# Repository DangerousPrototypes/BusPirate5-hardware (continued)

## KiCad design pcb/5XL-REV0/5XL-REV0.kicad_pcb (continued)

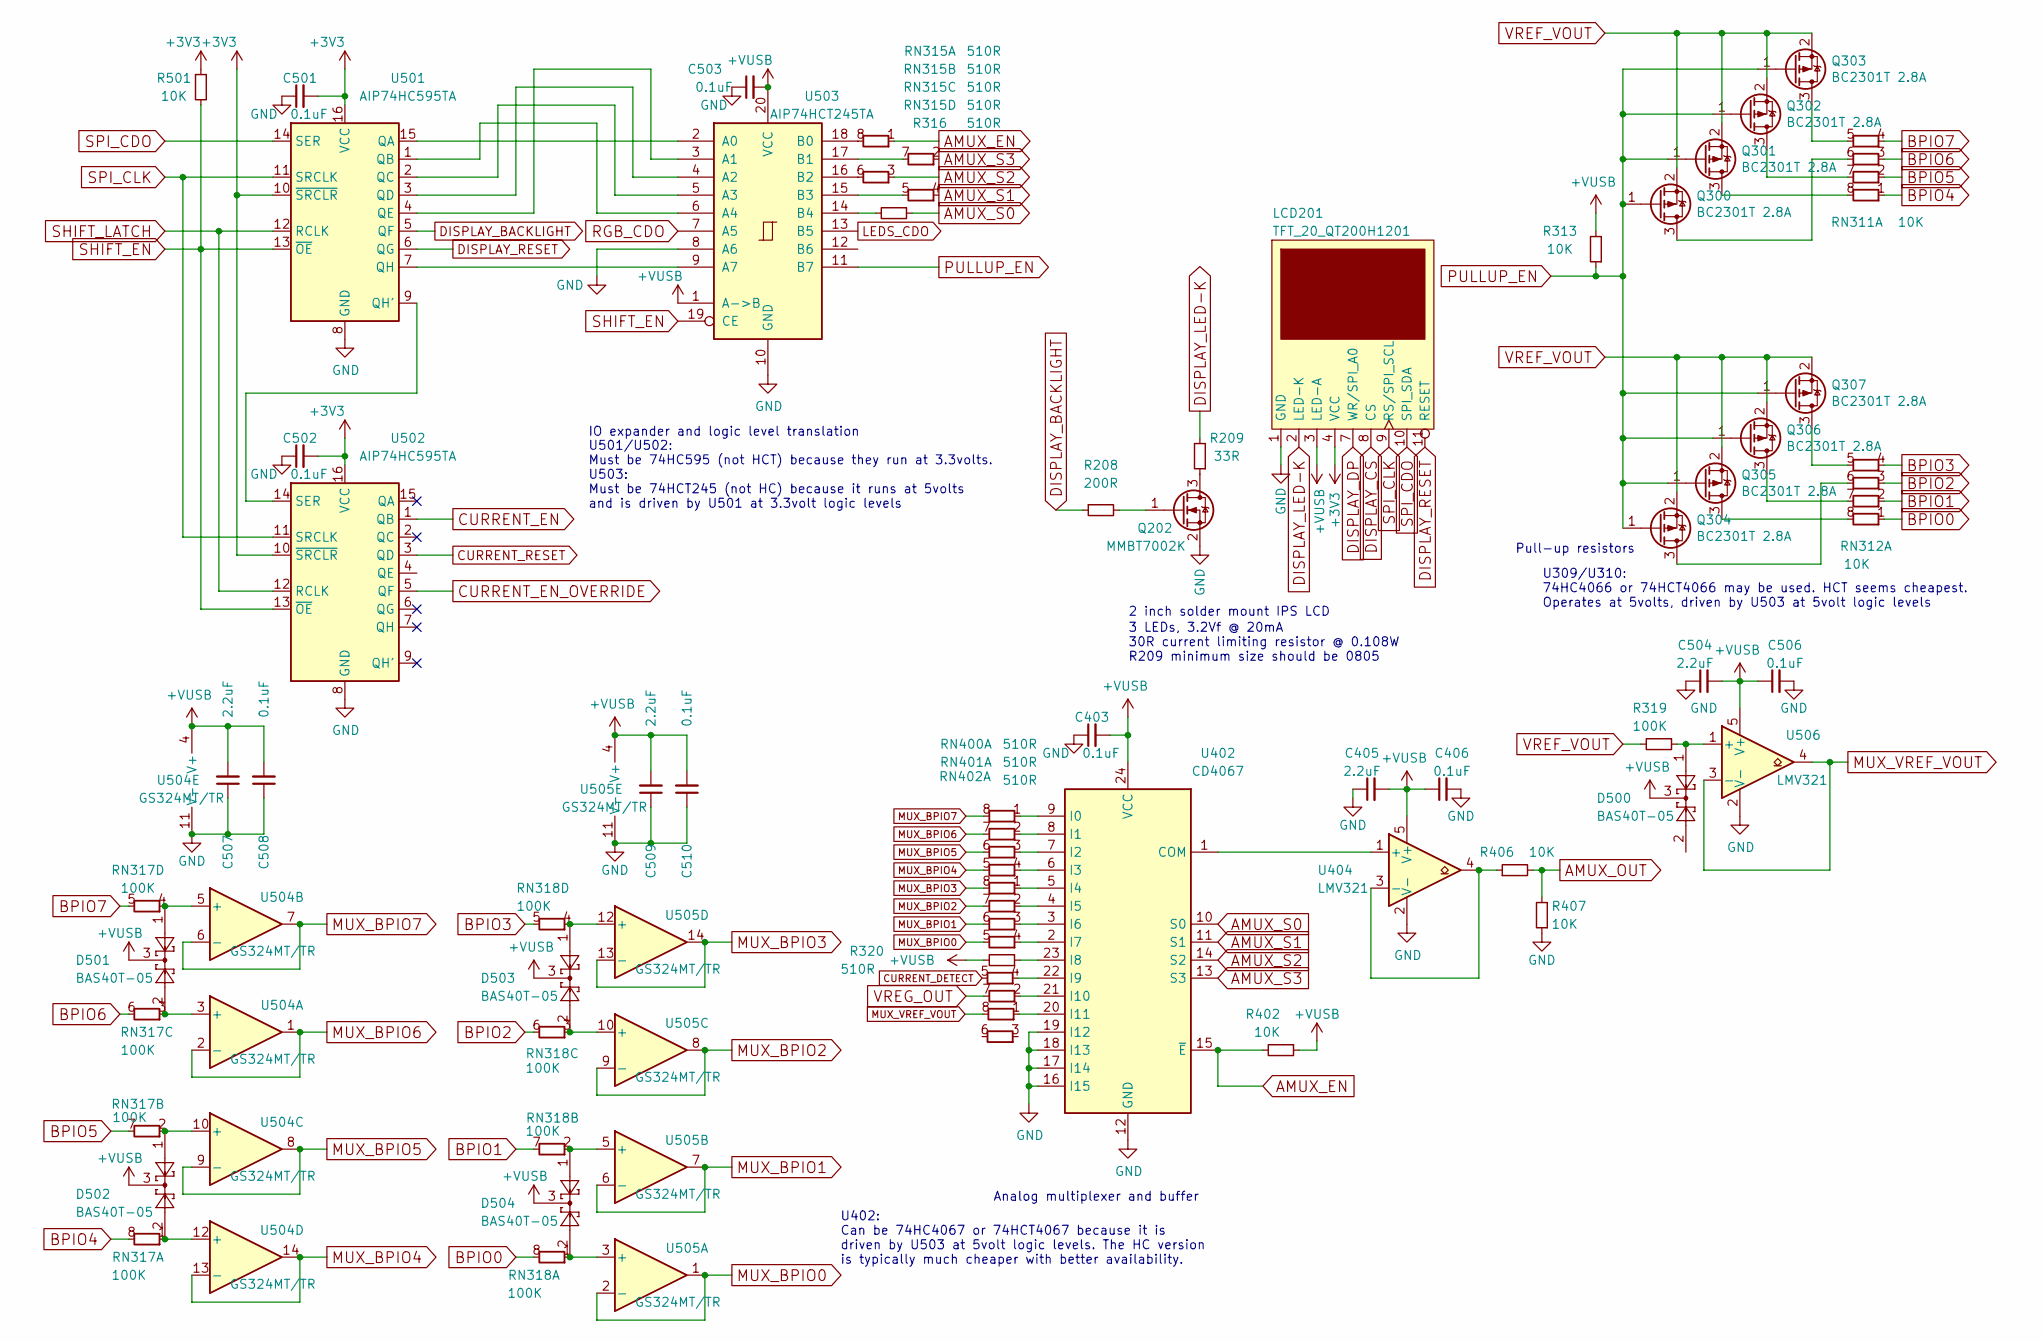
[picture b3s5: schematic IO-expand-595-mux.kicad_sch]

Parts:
C403, C406, C501, C502, C503, C506, C508, C510: 0.1uF; C_0402_1005Metric
C405, C504, C507, C509: 2.2uF; C_0402_1005Metric
D500, D501, D502, D503, D504: BAS40T-05; SOT-523
LCD201: TFT_20_QT200H1201
Q202: MMBT7002K; SOT-23
Q300, Q301, Q302, Q303, Q304, Q305, Q306, Q307: BC2301T 2.8A; SOT-523
R208: 200R; R_0402_1005Metric
R209: 33R; R_0805_2012Metric
R313, R402, R406, R407, R501: 10K; R_0402_1005Metric
R316, R320: 510R; R_0402_1005Metric
R319: 100K; R_0402_1005Metric
RN311, RN312: 10K; R_Array_Convex_4x0402
RN315, RN400, RN401, RN402: 510R; R_Array_Convex_4x0402
RN317, RN318: 100K; R_Array_Convex_4x0402
U402: CD4067; TSSOP-24_4.4x7.8mm_P0.65mm
U404, U506: LMV321; SOT-23-5
U501, U502: AIP74HC595TA; TSSOP-16_4.4x5mm_P0.65mm
U503: AIP74HCT245TA; TSSOP-20_4.4x6.5mm_P0.65mm
U504, U505: GS324MT/TR; TSSOP-14_4.4x5mm_P0.65mm

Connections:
+3V3: C501.2, C502.2, LCD201.4 (VCC), R501.1, U501.10 (~SRCLR), U501.16 (VCC), U502.10 (~SRCLR), U502.16 (VCC); also elsewhere on the board
+VUSB: C403.2, C405.2, C406.1, C503.2, C504.2, C506.1, C507.2, C508.2, C509.2, C510.2, D500.3, D501.3, D502.3, D503.3, D504.3, LCD201.3 (LED-A), R313.2, R320.2, R402.1, U402.24 (VCC), U404.5 (V+), U503.1 (A->B), U503.20 (VCC), U504.4 (V+), U505.4 (V+), U506.5 (V+); also elsewhere on the board
AMUX_EN: R402.2, RN315.1 (R1.1), U402.15 (~E)
AMUX_OUT: R406.2, R407.2; also elsewhere on the board
AMUX_S0: R316.1, U402.10 (S0)
AMUX_S1: RN315.4 (R1.1), U402.11 (S1)
AMUX_S2: RN315.3 (R1.1), U402.14 (S2)
AMUX_S3: RN315.2 (R1.1), U402.13 (S3)
BPIO0: RN312.1 (R1.1), RN318.8 (R1.8); also elsewhere on the board
BPIO1: RN312.2 (R1.1), RN318.7 (R1.8); also elsewhere on the board
BPIO2: RN312.3 (R1.1), RN318.6 (R1.8); also elsewhere on the board
BPIO3: RN312.4 (R1.1), RN318.5 (R1.8); also elsewhere on the board
BPIO4: RN311.1 (R1.1), RN317.8 (R1.8); also elsewhere on the board
BPIO5: RN311.2 (R1.1), RN317.7 (R1.8); also elsewhere on the board
BPIO6: RN311.3 (R1.1), RN317.6 (R1.8); also elsewhere on the board
BPIO7: RN311.4 (R1.1), RN317.5 (R1.8); also elsewhere on the board
CURRENT_DETECT: RN402.5 (R1.8); also elsewhere on the board
CURRENT_EN: U502.1 (QB); also elsewhere on the board
CURRENT_EN_OVERRIDE: U502.5 (QF); also elsewhere on the board
CURRENT_RESET: U502.3 (QD); also elsewhere on the board
DISPLAY_BACKLIGHT: R208.1, U501.5 (QF)
DISPLAY_CS: LCD201.8 (CS); also elsewhere on the board
DISPLAY_DP: LCD201.7 (WR/SPI_A0); also elsewhere on the board
DISPLAY_LED-K: LCD201.2 (LED-K), R209.2
DISPLAY_RESET: LCD201.11 (RESET), U501.6 (QG)
GND: C403.1, C405.1, C406.2, C501.1, C502.1, C503.1, C504.1, C506.2, C507.1, C508.1, C509.1, C510.1, LCD201.1 (GND), LCD201.5 (GND), LCD201.6 (GND), LCD201.12 (GND), Q202.2 (S), R407.1, U402.12 (GND), U402.16 (I15), U402.17 (I14), U402.18 (I13), U402.19 (I12), U404.2 (V-), U501.8 (GND), U502.8 (GND), U503.8 (A6), U503.10 (GND), U504.11 (V-), U505.11 (V-), U506.2 (V-); also elsewhere on the board
LEDS_CDO: U503.13 (B5); also elsewhere on the board
MUX_BPIO0: RN401.5 (R1.8), U505.1, U505.2 (-)
MUX_BPIO1: RN401.6 (R1.8), U505.6 (-), U505.7
MUX_BPIO2: RN401.7 (R1.8), U505.8, U505.9 (-)
MUX_BPIO3: RN401.8 (R1.8), U505.13 (-), U505.14
MUX_BPIO4: RN400.5 (R1.8), U504.13 (-), U504.14
MUX_BPIO5: RN400.6 (R1.8), U504.8, U504.9 (-)
MUX_BPIO6: RN400.7 (R1.8), U504.1, U504.2 (-)
MUX_BPIO7: RN400.8 (R1.8), U504.6 (-), U504.7
MUX_VREF_VOUT: RN402.8 (R1.8), U506.3 (-), U506.4
unnamed: Q202.3 (D), R209.1
unnamed: Q202.1 (G), R208.2
unnamed: Q300.3 (D), RN311.6 (R1.8)
unnamed: Q301.3 (D), RN311.8 (R1.8)
unnamed: Q302.3 (D), RN311.7 (R1.8)
unnamed: Q303.3 (D), RN311.5 (R1.8)
unnamed: Q304.3 (D), RN312.6 (R1.8)
unnamed: Q305.3 (D), RN312.8 (R1.8)
unnamed: Q306.3 (D), RN312.7 (R1.8)
unnamed: Q307.3 (D), RN312.5 (R1.8)
unnamed: RN315.8 (R1.8), U503.18 (B0)
unnamed: RN315.7 (R1.8), U503.17 (B1)
unnamed: RN315.6 (R1.8), U503.16 (B2)
unnamed: RN315.5 (R1.8), U503.15 (B3)
unnamed: D502.2, RN317.1 (R1.1), U504.12 (+)
unnamed: D502.1, RN317.2 (R1.1), U504.10 (+)
unnamed: D501.2, RN317.3 (R1.1), U504.3 (+)
unnamed: D501.1, RN317.4 (R1.1), U504.5 (+)
unnamed: D504.2, RN318.1 (R1.1), U505.3 (+)
unnamed: D504.1, RN318.2 (R1.1), U505.5 (+)
unnamed: D503.2, RN318.3 (R1.1), U505.10 (+)
unnamed: D503.1, RN318.4 (R1.1), U505.12 (+)
unnamed: RN400.1 (R1.1), U402.9 (I0)
unnamed: RN400.2 (R1.1), U402.8 (I1)
unnamed: RN400.3 (R1.1), U402.7 (I2)
unnamed: RN400.4 (R1.1), U402.6 (I3)
unnamed: RN401.1 (R1.1), U402.5 (I4)
unnamed: RN401.2 (R1.1), U402.4 (I5)
unnamed: RN401.3 (R1.1), U402.3 (I6)
unnamed: RN401.4 (R1.1), U402.2 (I7)
unnamed: RN402.1 (R1.1), U402.20 (I11)
unnamed: RN402.2 (R1.1), U402.21 (I10)
unnamed: RN402.4 (R1.1), U402.22 (I9)
unnamed: U402.1 (COM), U404.1 (+)
unnamed: R320.1, U402.23 (I8)
unnamed: R406.1, U404.3 (-), U404.4
unnamed: U501.15 (QA), U503.2 (A0)
unnamed: U501.1 (QB), U503.6 (A4)
unnamed: U501.2 (QC), U503.5 (A3)
unnamed: U501.3 (QD), U503.4 (A2)
unnamed: U501.4 (QE), U503.3 (A1)
unnamed: U501.9 (QH'), U502.14 (SER)
unnamed: U501.7 (QH), U503.9 (A7)
unnamed: R316.2, U503.14 (B4)
unnamed: D500.1, R319.1, U506.1 (+)
PULLUP_EN: Q300.1 (G), Q301.1 (G), Q302.1 (G), Q303.1 (G), Q304.1 (G), Q305.1 (G), Q306.1 (G), Q307.1 (G), R313.1, U503.11 (B7)
RGB_CDO: U503.7 (A5); also elsewhere on the board
SHIFT_EN: R501.2, U501.13 (~OE), U502.13 (~OE), U503.19 (CE); also elsewhere on the board
SHIFT_LATCH: U501.12 (RCLK), U502.12 (RCLK); also elsewhere on the board
SPI_CDO: LCD201.10 (SPI_SDA), U501.14 (SER); also elsewhere on the board
SPI_CLK: LCD201.9 (RS/SPI_SCL), U501.11 (SRCLK), U502.11 (SRCLK); also elsewhere on the board
VREF_VOUT: Q300.2 (S), Q301.2 (S), Q302.2 (S), Q303.2 (S), Q304.2 (S), Q305.2 (S), Q306.2 (S), Q307.2 (S), R319.2; also elsewhere on the board
VREG_OUT: RN402.7 (R1.8); also elsewhere on the board

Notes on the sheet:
IO expander and logic level translation
Analog multiplexer and buffer
U402: Can be 74HC4067 or 74HCT4067 because it is driven by U503 at 5volt logic levels. The HC version is typically much cheaper with better availability.
3 LEDs, 3.2Vf @ 20mA 30R current limiting resistor @ 0.108W R209 minimum size should be 0805
2 inch solder mount IPS LCD
U501/U502: Must be 74HC595 (not HCT) because they run at 3.3volts. U503: Must be 74HCT245 (not HC) because it runs at 5volts and is driven by U501 at 3.3volt logic levels
U309/U310: 74HC4066 or 74HCT4066 may be used. HCT seems cheapest. Operates at 5volts, driven by U503 at 5volt logic levels
Pull-up resistors

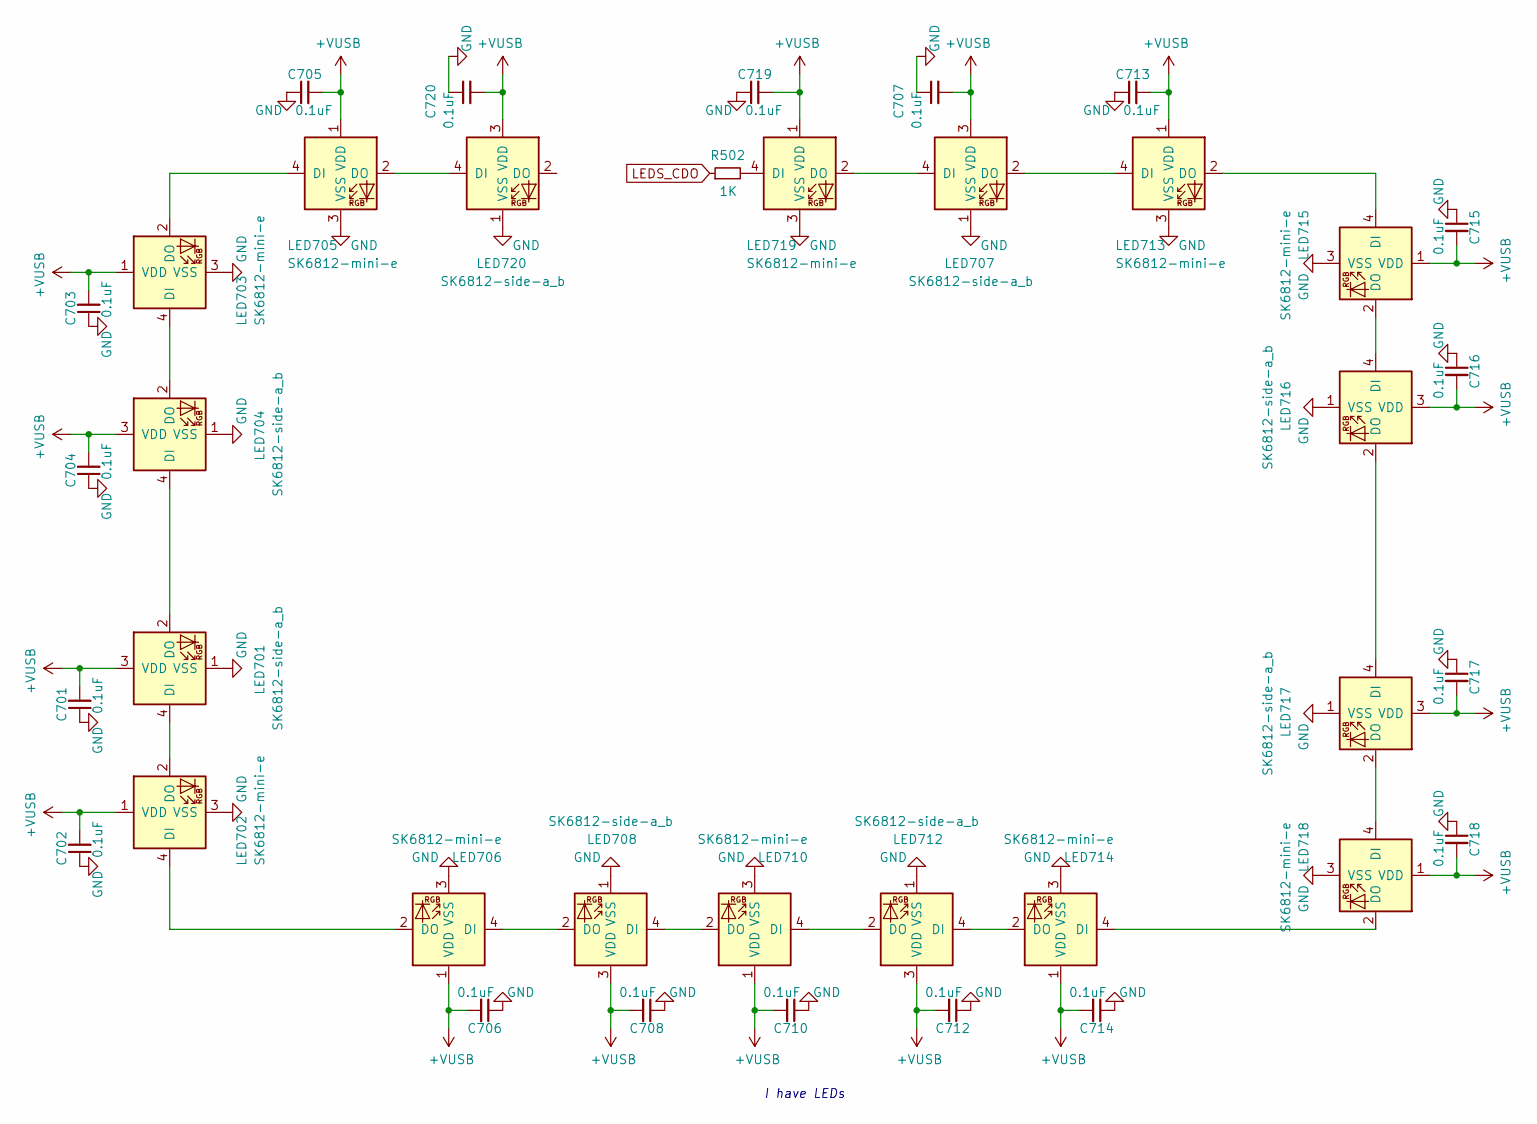
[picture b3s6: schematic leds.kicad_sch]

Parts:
C701, C702, C703, C704, C705, C706, C707, C708, C710, C712, C713, C714, C715, C716, C717, C718, C719, C720: 0.1uF; C_0402_1005Metric
LED701, LED704, LED707, LED708, LED712, LED716, LED717, LED720: SK6812-side-a_b
LED702, LED703, LED705, LED706, LED710, LED713, LED714, LED715, LED718, LED719: SK6812-mini-e
R502: 1K; R_0402_1005Metric

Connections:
+VUSB: C701.2, C702.2, C703.2, C704.2, C705.2, C706.2, C707.2, C708.2, C710.2, C712.2, C713.2, C714.2, C715.2, C716.2, C717.2, C718.2, C719.2, C720.2, LED701.3 (VDD), LED702.1 (VDD), LED703.1 (VDD), LED704.3 (VDD), LED705.1 (VDD), LED706.1 (VDD), LED707.3 (VDD), LED708.3 (VDD), LED710.1 (VDD), LED712.3 (VDD), LED713.1 (VDD), LED714.1 (VDD), LED715.1 (VDD), LED716.3 (VDD), LED717.3 (VDD), LED718.1 (VDD), LED719.1 (VDD), LED720.3 (VDD); also elsewhere on the board
GND: C701.1, C702.1, C703.1, C704.1, C705.1, C706.1, C707.1, C708.1, C710.1, C712.1, C713.1, C714.1, C715.1, C716.1, C717.1, C718.1, C719.1, C720.1, LED701.1 (VSS), LED702.3 (VSS), LED703.3 (VSS), LED704.1 (VSS), LED705.3 (VSS), LED706.3 (VSS), LED707.1 (VSS), LED708.1 (VSS), LED710.3 (VSS), LED712.1 (VSS), LED713.3 (VSS), LED714.3 (VSS), LED715.3 (VSS), LED716.1 (VSS), LED717.1 (VSS), LED718.3 (VSS), LED719.3 (VSS), LED720.1 (VSS); also elsewhere on the board
LEDS_CDO: R502.1; also elsewhere on the board
unnamed: LED701.4 (DI), LED702.2 (DO)
unnamed: LED701.2 (DO), LED704.4 (DI)
unnamed: LED702.4 (DI), LED706.2 (DO)
unnamed: LED703.4 (DI), LED704.2 (DO)
unnamed: LED703.2 (DO), LED705.4 (DI)
unnamed: LED705.2 (DO), LED720.4 (DI)
unnamed: LED706.4 (DI), LED708.2 (DO)
unnamed: LED707.4 (DI), LED719.2 (DO)
unnamed: LED707.2 (DO), LED713.4 (DI)
unnamed: LED708.4 (DI), LED710.2 (DO)
unnamed: LED710.4 (DI), LED712.2 (DO)
unnamed: LED712.4 (DI), LED714.2 (DO)
unnamed: LED713.2 (DO), LED715.4 (DI)
unnamed: LED714.4 (DI), LED718.2 (DO)
unnamed: LED715.2 (DO), LED716.4 (DI)
unnamed: LED716.2 (DO), LED717.4 (DI)
unnamed: LED717.2 (DO), LED718.4 (DI)
unnamed: LED719.4 (DI), R502.2

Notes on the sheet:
I have LEDs

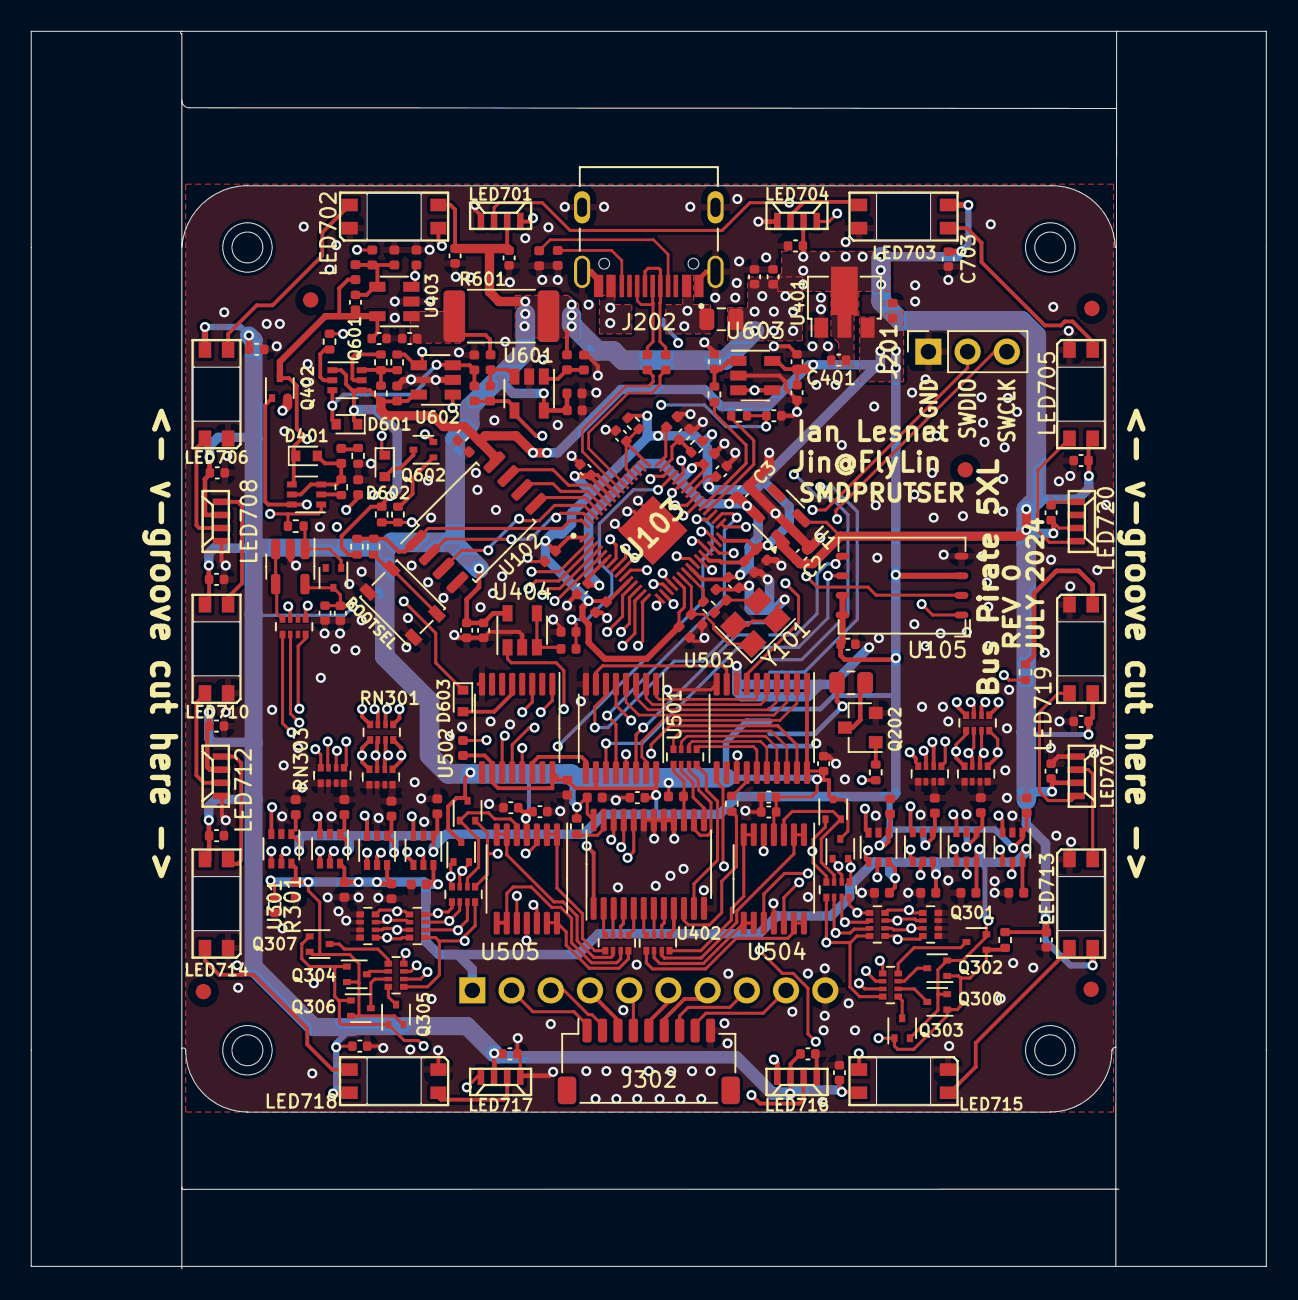
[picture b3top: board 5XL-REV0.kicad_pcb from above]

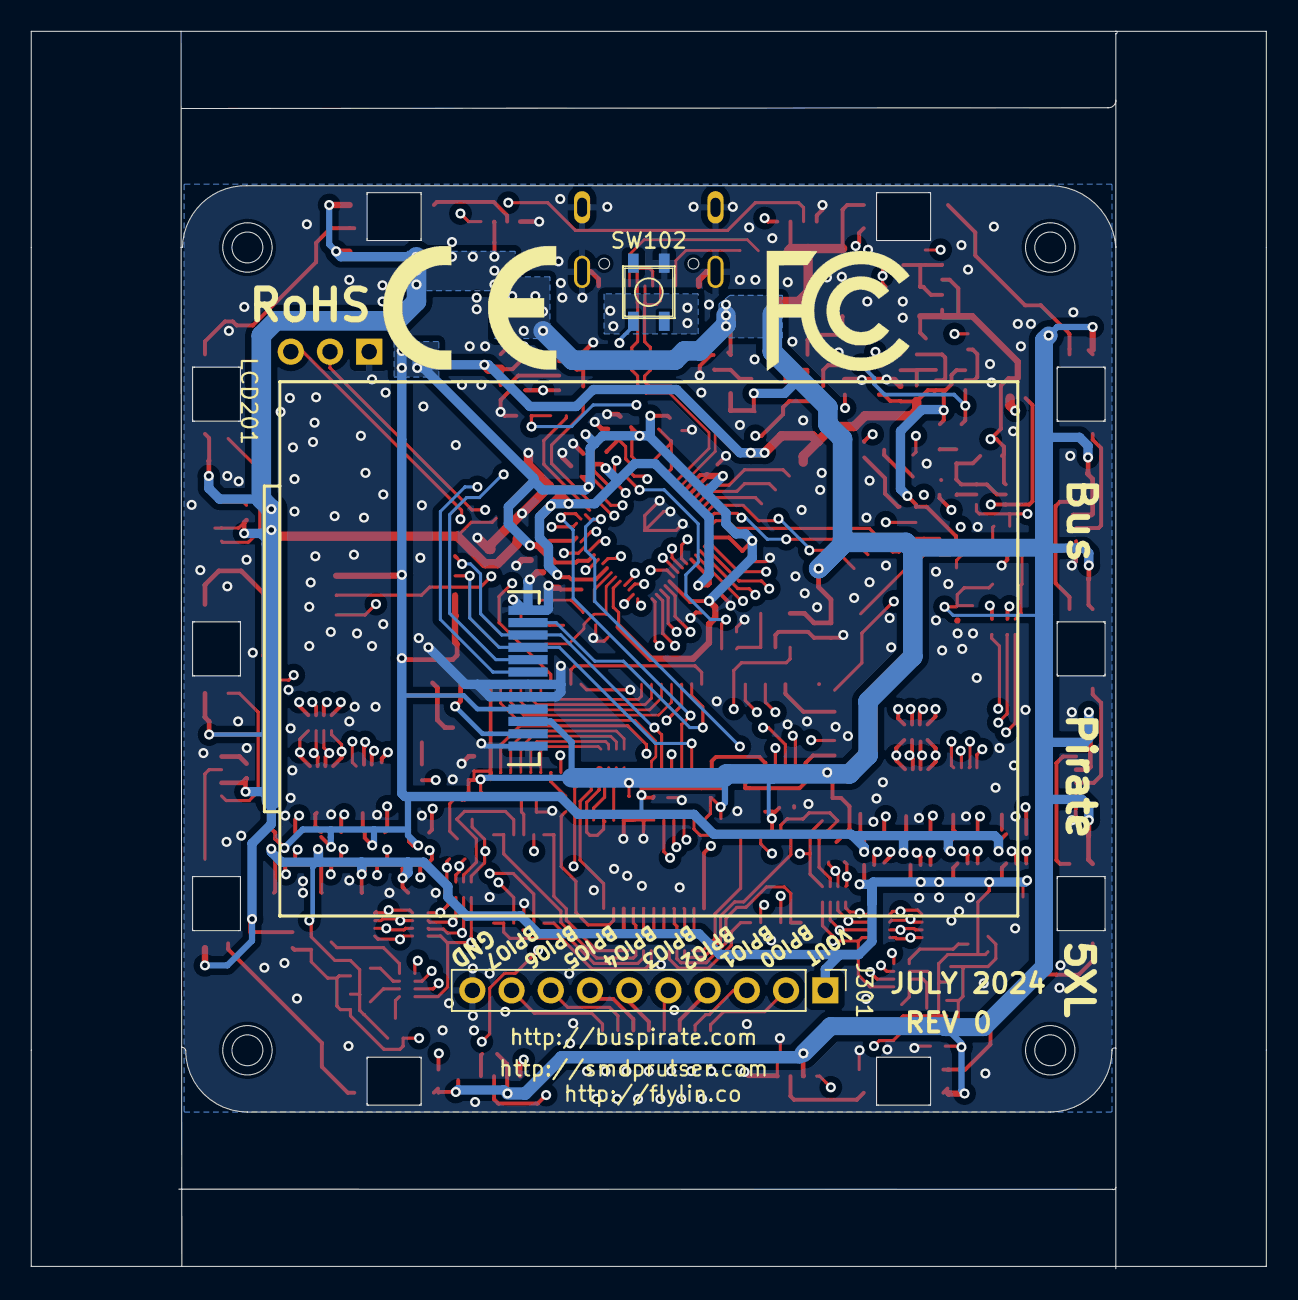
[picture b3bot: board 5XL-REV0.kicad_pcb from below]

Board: 4 copper layers, 80.0 x 80.0 mm, 227 parts (5 on the bottom side), 185 nets.
